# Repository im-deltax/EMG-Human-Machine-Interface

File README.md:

# EMG Human–Machine Interface

An eight-channel EMG hardware research project by Trần Minh Triết (im-deltax), intended to explore assistive human–computer interaction for people with disabilities using muscle signals.

## PCB-only publication

This repository contains the existing `EMG8_Wireless.kicad_pcb`, its KiCad project settings, and the project-local footprint library required for editing. Open the PCB with KiCad 9. The schematic, datasets, AI training code, simulations, backups and unrelated files are intentionally not included in this PCB-only publication. PCB filename and geometry are unchanged from the supplied source.

The intended assistive interaction features are development goals, not demonstrated outcomes of this release. Firmware, a working computer-control application and user-study results are not included.

## Verification status

The supplied historical `DRC_RevB_final.rpt` reports 10 warning-level violations, 0 unconnected pads and 0 footprint errors. That report is not a fresh check of this publication, and DRC has not been rerun here. Other historical documents describe different design revisions; their release-ready claims are not adopted by this repository.

No fabrication, electrical bring-up, human-use safety validation or assistive-performance validation is established by this publication. This is a research design, not a certified medical device. The supplied source notes shared USB ground and unverified isolation; do not infer suitability for connecting electrodes to a person from these files.

## Licensing and attribution

No new blanket license is assigned to the author's PCB design in this publication. The license selected for Robodeltax does not automatically apply to this separate project. Third-party library notices are retained in [THIRD_PARTY.md](THIRD_PARTY.md) and [LICENSE_KiCad_Libraries.md](LICENSE_KiCad_Libraries.md). These files describe library sources; their inclusion does not imply the full original schematic or every referenced component is included here.

## Tiếng Việt

Dự án nghiên cứu thiết bị EMG tám kênh nhằm hỗ trợ người khuyết tật tương tác với máy tính bằng tín hiệu cơ. Bản này chỉ công khai PCB và tài nguyên KiCad cần thiết, không gồm dataset, AI, mô phỏng hoặc firmware. Chưa chạy lại DRC, chưa xác nhận hoạt động trên bo thật hoặc hiệu quả sử dụng hỗ trợ tiếp cận. Giấy phép riêng cho thiết kế PCB chưa được chọn.

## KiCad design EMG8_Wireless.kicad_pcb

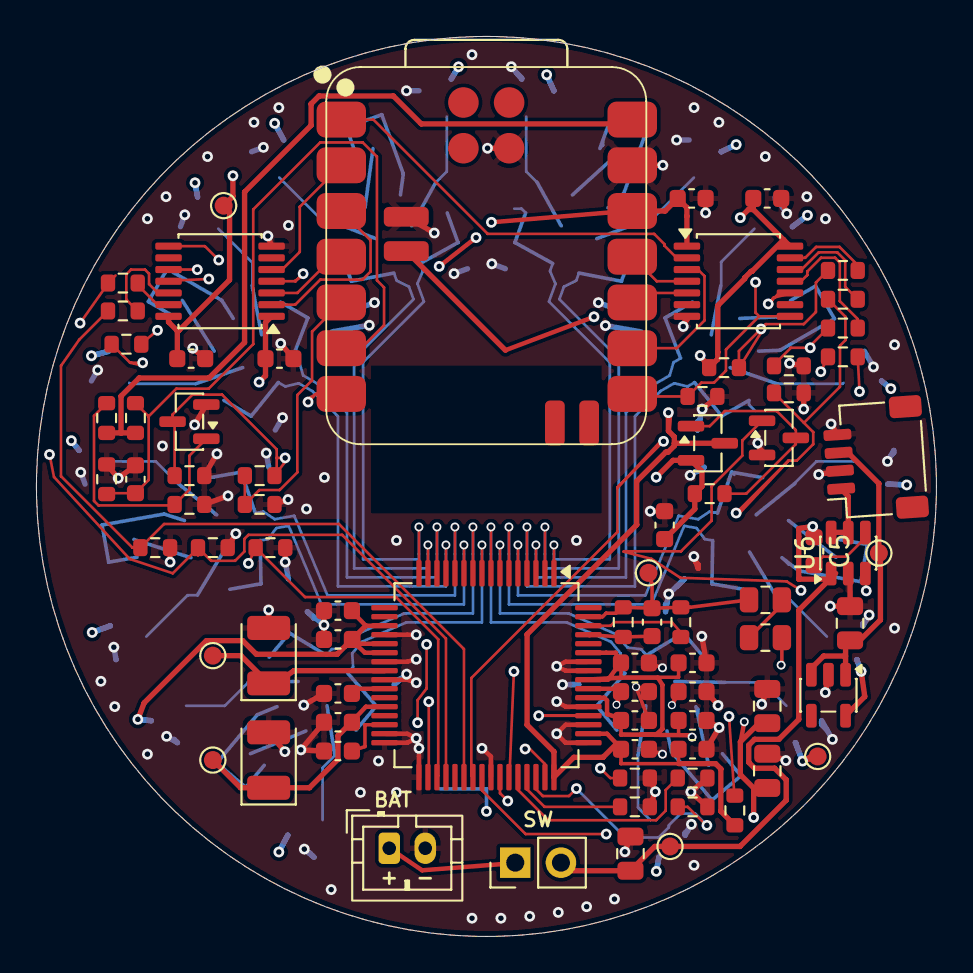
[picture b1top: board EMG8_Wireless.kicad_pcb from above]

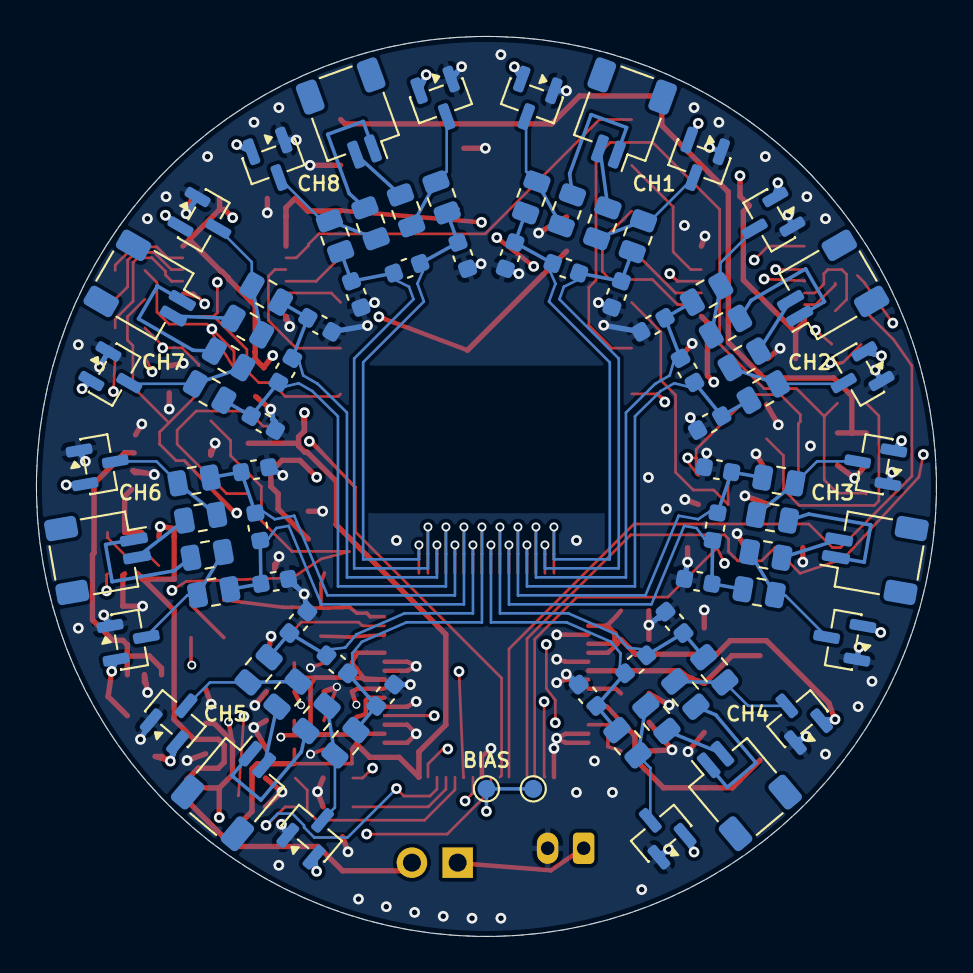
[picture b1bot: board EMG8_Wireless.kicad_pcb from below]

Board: 4 copper layers, 50.0 x 50.0 mm, 159 parts (82 on the bottom side), 102 nets.

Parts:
C1, C4: 10uF / 10V X7R; C_0805
C2, C3: 2.2uF / 10V X7R; C_0805
C5: 1nF / 25V X7R; C_0603
C10, C12, C14, C16, C22, C23, C25, C42: 1uF / 10V X7R; C_0603
C11, C13, C15, C17, C21, C24, C43, C44, C45, C46: 100nF / 10V X7R; C_0603
C20: 100uF / 6.3V tantalum; C_TANT_B
C26: 22uF / 10V tantalum; C_TANT_B
C40: 470p / C0G 50V; C_0603
C41: 10n / X7R; C_0603
C110, C111, C120, C121, C130, C131, C140, C141, C150, C151, C160, C161, C170, C171, C180, C181: 10p / C0G; C_0603
C112, C122, C132, C142, C152, C162, C172, C182: 220p / C0G; C_0603
D1, D2, D3, D4, D5, D6, D7, D8, D9, D10, D11, D12, D13, D14, D15, D16: BAV99; SOT23
J1: LiPo 1S / protected; JST_PH2
J2: MT3608 / external; JST_SH4
J11: CH1 P / N; JST_SH2
J12: CH2 P / N; JST_SH2
J13: CH3 P / N; JST_SH2
J14: CH4 P / N; JST_SH2
J15: CH5 P / N; JST_SH2
J16: CH6 P / N; JST_SH2
J17: CH7 P / N; JST_SH2
J18: CH8 P / N; JST_SH2
J20: BIAS electrode; TP_1MM
Q2: AO3401A; SOT23
Q4: MMBT3904; SOT23
Q5: BSS138BK; SOT23
R2, R6, R21, R30, R31, R32, R33: 10k; R_0603
R3, R4, R22, R23, R24, R25, R26, R40, R46, R47, R48: 100k; R_0603
R5, R44: 1M; R_0603
R10, R11, R12, R13, R14, R15, R20: 33; R_0603
R41, R42: 1M; R_0805
R43: 0; R_0603
R45: 470k; R_0603
R110, R111, R112, R113, R120, R121, R122, R123, R130, R131, R132, R133, R140, R141, R142, R143, R150, R151, R152, R153, R160, R161, R162, R163, R170, R171, R172, R173, R180, R181, R182, R183: 120k; R_0805
SW1: MAIN / external switch; HDR2
TP1: VBAT_SYS; TP_1MM
TP2: DVDD_3V3; TP_1MM
TP3: BOOST_5V4; TP_1MM
TP5: AVDD_5V; TP_1MM
TP6: VCAP1; TP_1MM
TP7: VREFP; TP_1MM
TP8: BIASOUT; TP_1MM
TP9: BIAS_ELECTRODE; TP_1MM
U1: ADS1299IPAG; TQFP64
U2: XIAO nRF52840; XIAO_nRF52840_SMD
U3: TPS7A2050PDBVR; SOT23_5
U4, U5: TXU0304PWR; TSSOP14
U6: TPS22917DBVR; SOT23_6

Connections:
3V3_MCU: C42.1, C43.1, C45.1, Q2.2 (S), R6.1, U2.12 (3V3_OUT), U4.1 (VCCA), U5.1 (VCCA)
ADS_CLKSEL: R21.2, U1.52 (CLKSEL)
ADS_CS: R10.1, R22.2, U1.39 (~CS)
ADS_DIN: R15.1, R47.1, U1.34 (DIN)
ADS_DOUT: R20.1, U1.43 (DOUT)
ADS_DRDY: U1.47 (~DRDY), U5.10 (B4)
ADS_GPIO1: R30.1, U1.42 (GPIO1)
ADS_GPIO2: R31.1, U1.44 (GPIO2)
ADS_GPIO3: R32.1, U1.45 (GPIO3)
ADS_GPIO4: R33.1, U1.46 (GPIO4)
ADS_PWDN: R13.1, R25.1, U1.35 (~PWDN)
ADS_RESET: R11.1, R24.1, U1.36 (~RESET)
ADS_SCLK: R14.1, R48.1, U1.40 (SCLK)
ADS_START: R12.1, R23.1, U1.38 (START)
AFE_BASE: Q4.3 (C), Q5.1 (G), R2.2, R3.1, U6.3 (ON)
AFE_CT: C5.2, U6.4 (CT)
AFE_EN: R2.1, R26.1, U2.5 (D4_/_AFE_EN)
AFE_IO_EN: R46.1, U2.8 (D7_/_AFE_IO_EN), U4.8 (OE), U5.8 (OE)
AVDD_5V: C3.1, C4.1, C10.1, C11.1, C12.1, C13.1, C14.1, C15.1, D1.2 (K), D2.2 (K), D3.2 (K), D4.2 (K), D5.2 (K), D6.2 (K), D7.2 (K), D8.2 (K), D9.2 (K), D10.2 (K), D11.2 (K), D12.2 (K), D13.2 (K), D14.2 (K), D15.2 (K), D16.2 (K), TP5.1, U1.19 (AVDD), U1.21 (AVDD), U1.22 (AVDD), U1.54 (AVDD1), U1.56 (AVDD), U1.59 (AVDD), U3.5 (OUT)
BAT_RAW: J1.1, SW1.1
BIASIN: R43.2, U1.62 (BIASIN)
BIASINV: C40.2, R40.2, U1.61 (BIASINV)
BIASOUT: C40.1, R40.1, R41.1, R43.1, TP8.1, U1.63 (BIASOUT)
BIAS_ELECTRODE: J20.1, R42.2, TP9.1
BIAS_LIMIT_MID: R41.2, R42.1
BOOST_5V4: C2.1, J2.3 (VOUT+), TP3.1, U3.1 (IN), U3.3 (EN)
BUF_CS: R10.2, U4.13 (B1Y)
BUF_DIN: R15.2, U4.11 (B3Y)
BUF_PWDN: R13.2, U5.11 (B3Y)
BUF_RESET: R11.2, U5.13 (B1Y)
BUF_SCLK: R14.2, U4.12 (B2Y)
BUF_START: R12.2, U5.12 (B2Y)
CH1_N: C111.1, C112.2, R113.2, U1.15 (IN1N)
CH1_P: C110.1, C112.1, R111.2, U1.16 (IN1P)
CH2_N: C121.1, C122.2, R123.2, U1.13 (IN2N)
CH2_P: C120.1, C122.1, R121.2, U1.14 (IN2P)
CH3_N: C131.1, C132.2, R133.2, U1.11 (IN3N)
CH3_P: C130.1, C132.1, R131.2, U1.12 (IN3P)
CH4_N: C141.1, C142.2, R143.2, U1.9 (IN4N)
CH4_P: C140.1, C142.1, R141.2, U1.10 (IN4P)
CH5_N: C151.1, C152.2, R153.2, U1.7 (IN5N)
CH5_P: C150.1, C152.1, R151.2, U1.8 (IN5P)
CH6_N: C161.1, C162.2, R163.2, U1.5 (IN6N)
CH6_P: C160.1, C162.1, R161.2, U1.6 (IN6P)
CH7_N: C171.1, C172.2, R173.2, U1.3 (IN7N)
CH7_P: C170.1, C172.1, R171.2, U1.4 (IN7P)
CH8_N: C181.1, C182.2, R183.2, U1.1 (IN8N)
CH8_P: C180.1, C182.1, R181.2, U1.2 (IN8P)
DVDD_3V3: C16.1, C17.1, C44.1, C46.1, Q2.3 (D), R21.1, R22.1, TP2.1, U1.48 (DVDD), U1.50 (DVDD), U4.14 (VCCB), U5.14 (VCCB)
DVDD_GATE: Q2.1 (G), Q5.3 (D), R6.2
GND: C1.2, C2.2, C3.2, C4.2, C10.2, C11.2, C12.2, C13.2, C14.2, C15.2, C16.2, C17.2, C20.2, C21.2, C22.2, C23.2, C24.2, C25.2, C26.2, C41.2, C42.2, C43.2, C44.2, C45.2, C46.2, C110.2, C111.2, C120.2, C121.2, C130.2, C131.2, C140.2, C141.2, C150.2, C151.2, C160.2, C161.2, C170.2, C171.2, C180.2, C181.2, D1.1 (A), D2.1 (A), D3.1 (A), D4.1 (A), D5.1 (A), D6.1 (A), D7.1 (A), D8.1 (A), D9.1 (A), D10.1 (A), D11.1 (A), D12.1 (A), D13.1 (A), D14.1 (A), D15.1 (A), D16.1 (A), J1.2, J2.2 (VIN-), J2.4 (VOUT-), Q4.2 (E), Q5.2 (S), R3.2, R5.2, R23.2, R24.2, R25.2, R26.2, R30.2, R31.2, R32.2, R33.2, R45.2, R46.2, R47.2, R48.2, U1.20 (AVSS), U1.23 (AVSS), U1.25 (VREFN), U1.31 (RESV1), U1.32 (AVSS), U1.33 (DGND), U1.41 (DAISY_IN), U1.49 (DGND), U1.51 (DGND), U1.53 (AVSS1), U1.57 (AVSS), U1.58 (AVSS), U2.13 (GND), U2.18 (GND_(rear)), U2.20 (BAT-_(rear)), U3.2 (GND), U4.7 (GND), U5.7 (GND), U6.2 (GND)
MCU_CS: U2.1 (D0_/_CS), U4.2 (A1)
MCU_DIN: U2.11 (D10_/_MOSI), U4.4 (A3)
MCU_DRDY: U2.2 (D1_/_DRDY), U5.5 (A4Y)
MCU_MISO: U2.10 (D9_/_MISO), U4.5 (A4Y)
MCU_PWDN: U2.7 (D6_/_PWDN), U5.4 (A3)
MCU_RESET: U2.3 (D2_/_RESET), U5.2 (A1)
MCU_SCLK: U2.9 (D8_/_SCK), U4.3 (A2)
MCU_START: U2.4 (D3_/_START), U5.3 (A2)
unnamed: D1.3 (common), R110.2, R111.1
unnamed: D2.3 (common), R112.2, R113.1
unnamed: D3.3 (common), R120.2, R121.1
unnamed: D4.3 (common), R122.2, R123.1
unnamed: D5.3 (common), R130.2, R131.1
unnamed: D6.3 (common), R132.2, R133.1
unnamed: D7.3 (common), R140.2, R141.1
unnamed: D8.3 (common), R142.2, R143.1
unnamed: D9.3 (common), R150.2, R151.1
unnamed: D10.3 (common), R152.2, R153.1
unnamed: D11.3 (common), R160.2, R161.1
unnamed: D12.3 (common), R162.2, R163.1
unnamed: D13.3 (common), R170.2, R171.1
unnamed: D14.3 (common), R172.2, R173.1
unnamed: D15.3 (common), R180.2, R181.1
unnamed: D16.3 (common), R182.2, R183.1
unnamed: J11.1, R110.1
unnamed: J11.2, R112.1
unnamed: J12.1, R120.1
unnamed: J12.2, R122.1
unnamed: J13.1, R130.1
unnamed: J13.2, R132.1
unnamed: J14.1, R140.1
unnamed: J14.2, R142.1
unnamed: J15.1, R150.1
unnamed: J15.2, R152.1
unnamed: J16.1, R160.1
unnamed: J16.2, R162.1
unnamed: J17.1, R170.1
unnamed: J17.2, R172.1
unnamed: J18.1, R180.1
unnamed: J18.2, R182.1
SPI_MISO: R20.2, U4.10 (B4)
USB_INHIBIT_BASE: Q4.1 (B), R4.2, R5.1
USB_VBUS: R4.1, R44.1, U2.14 (VBUS_/_USB_5V)
VBAT_AFE: J2.1 (VIN+), U6.5 (QOD), U6.6 (VOUT)
VBAT_SYS: C1.1, C5.1, SW1.2, TP1.1, U2.19 (VBAT_(rear_pad)), U6.1 (VIN)
VBUS_SENSE: C41.1, R44.2, R45.1, U2.6 (D5_/_VBUS_ADC)
VCAP1: C20.1, C21.1, TP6.1, U1.28 (VCAP1)
VCAP2: C22.1, U1.30 (VCAP2)
VCAP3: C23.1, C24.1, U1.55 (VCAP3)
VCAP4: C25.1, U1.26 (VCAP4)
VREFP: C26.1, TP7.1, U1.24 (VREFP)
